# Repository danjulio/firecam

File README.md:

# firecam
 ESP32 code for the Fire CAM Thermal Imager

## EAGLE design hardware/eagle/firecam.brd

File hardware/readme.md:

## FireCAM Hardware
This directory contains hardware design files.  Schematic entry and PCB layout was done using Eagle 7.7.

* display_mount - DXF and SVG files for a laser cut plastic display mount, OpenSCAD and STL files for a 3-piece 3D printed base and display mount.
* documentation - BOM, schematic, PCB image and helpful list of componentst to load on the PCB.
* eagle - Schematic and PCB Layout design files.
* gerber - PCB gerber files
* stencil - Stencil gerber files

### Parts
Two shared Mouser BOMs are available for most of the components.

1. [FireCAM Rev 3 PCB Parts](https://www.mouser.com/ProjectManager/ProjectDetail.aspx?AccessID=e3b4e6fe5d) - Parts for direct mounting on the PCB.
2. [FireCAM Rev 3 Assembly Parts](https://www.mouser.com/ProjectManager/ProjectDetail.aspx?AccessID=ba0938d0f0) - Additional assembly parts.

In addition a commonly available 2.8" ILI9341/XPT2046 LCD display is used.  I have successfully sourced many units from the [HiLetGo](https://www.amazon.com/HiLetgo-240X320-Resolution-Display-ILI9341/dp/B073R7BH1B) store on Amazon but they are available from many sources.  You will also need some flexible 28 AWG silicon hook-up wire and heat shrink to make the Temperature Sensor and LCD wiring harnesses and a Micro-SD Card.

### Main PCB

### Subassemblies

#### Temperature probe
The TMP36 temperature sensor is connected to a 3-pin male 0.1" (2.54mm) using 3 2" (51 mm) 28 AWG wires.  Heatshrink each individual connection and the wire assembly to each of the connector and temperature sensor.  Note the orientation of the sensor relative to the connections on the PCB.

#### Display wiring harness
The Display harness contains the shared SPI bus for the LCD and Touchscreen, control, and power signals.  The shared SPI bus signals are connected at the display side in order to minimize signal reflections.

#### 3D Printed Base and Display Mount
A base and two-piece display mount may be printed by slicing the STL files for your particular printer.  The STL was generated using OpenSCAD and the source files included here.

#### Laser Cut Display Mount
The display mount is designed to be cut from a piece of 1/8" plastic on a laser cutter.

### Enclosure
FireCAM is released without an enclosure as the original client for the project built their own custom enclosure for it.

### Expansion Ports

1. I2C Bus
2. ADC inputs A0 and A1 (not currently used by the firmware)

### Important Notes

1. Do not insert the LiPo battery backwards!  This will damage the camera electronics.
2. The RTC has a higher-than normal draw from the coin cell until it has been initialized.  Load firmware before inserting the coin cell and then immediately power on the camera to initialize the RTC (even if it has the wrong time).
3. Do not enable WiFi unless the antenna is connected.  It is possible to damage the ESP32 without an antenna.
4. The camera is charged from the USB port.  It will take a maximum of 500 mA from this port if it detects a charger attached (D+ connected to D-) or the USB port has been enumerated by an attached computer.  It will take a maximum of 100 mA from this port when attached to a computer but not enumerated.  It will suspect power draw when the USB bus is suspended (e.g. computer is put to sleep).  Current is shared between charging the battery and power the camera so the battery will charge faster if the camera is powered off.  The red LED lights while charging.  It will not charge if D+/D- are not connected together or connected to a computer USB port.  Most USB chargers will work.

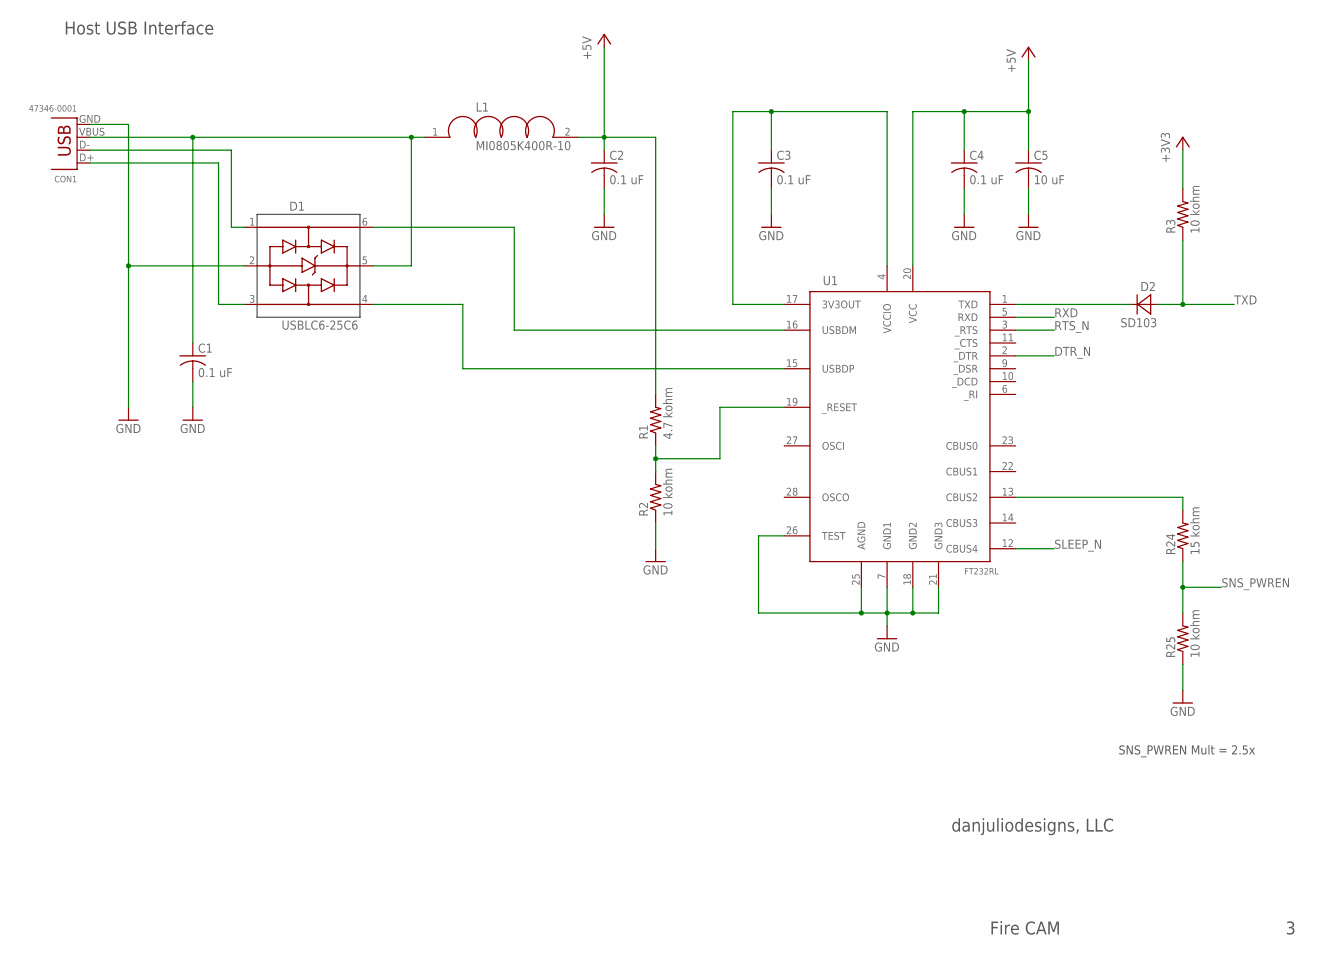
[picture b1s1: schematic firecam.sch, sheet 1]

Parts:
C1, C2, C3, C4: 0.1 uF; C0603
C5: 10 uF; C0603
CON1: 47346-0001; USB_MICROB_SMT
D1: USBLC6-25C6; SOT23-6
D2: SD103; SOD123
L1: MI0805K400R-10; L0805
R1: 4.7 kohm; R0603
R2, R3, R25: 10 kohm; R0603
R24: 15 kohm; R0603
U1: FT232RL; SSOP28DB

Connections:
+3V3: R3.2; also elsewhere on the board
+5V: C2.1, C4.1, C5.1, L1.2, R1.2, U1.20 (VCC); also elsewhere on the board
DTR_N: U1.2 (_DTR); also elsewhere on the board
GND: C1.2, C2.2, C3.2, C4.2, C5.2, CON1.GND, D1.2 (GND), R2.1, R25.1, U1.7 (GND1), U1.18 (GND2), U1.21 (GND3), U1.25 (AGND), U1.26 (TEST); also elsewhere on the board
unnamed: C1.1, CON1.VBUS, D1.5 (VBUS), L1.1
unnamed: CON1.D+, D1.3 (IO2)
unnamed: CON1.D-, D1.1 (IO1)
unnamed: C3.1, U1.4 (VCCIO), U1.17 (3V3OUT)
unnamed: D2.C, U1.1 (TXD)
unnamed: D1.6 (IO1$1), U1.16 (USBDM)
unnamed: D1.4 (IO2$1), U1.15 (USBDP)
unnamed: R1.1, R2.2, U1.19 (_RESET)
unnamed: R24.2, U1.13 (CBUS2)
RTS_N: U1.3 (_RTS); also elsewhere on the board
RXD: U1.5 (RXD); also elsewhere on the board
SLEEP_N: U1.12 (CBUS4); also elsewhere on the board
SNS_PWREN: R24.1, R25.2; also elsewhere on the board
TXD: D2.A, R3.1; also elsewhere on the board

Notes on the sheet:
danjuliodesigns, LLC
Fire CAM
Host USB Interface
SNS_PWREN Mult = 2.5x

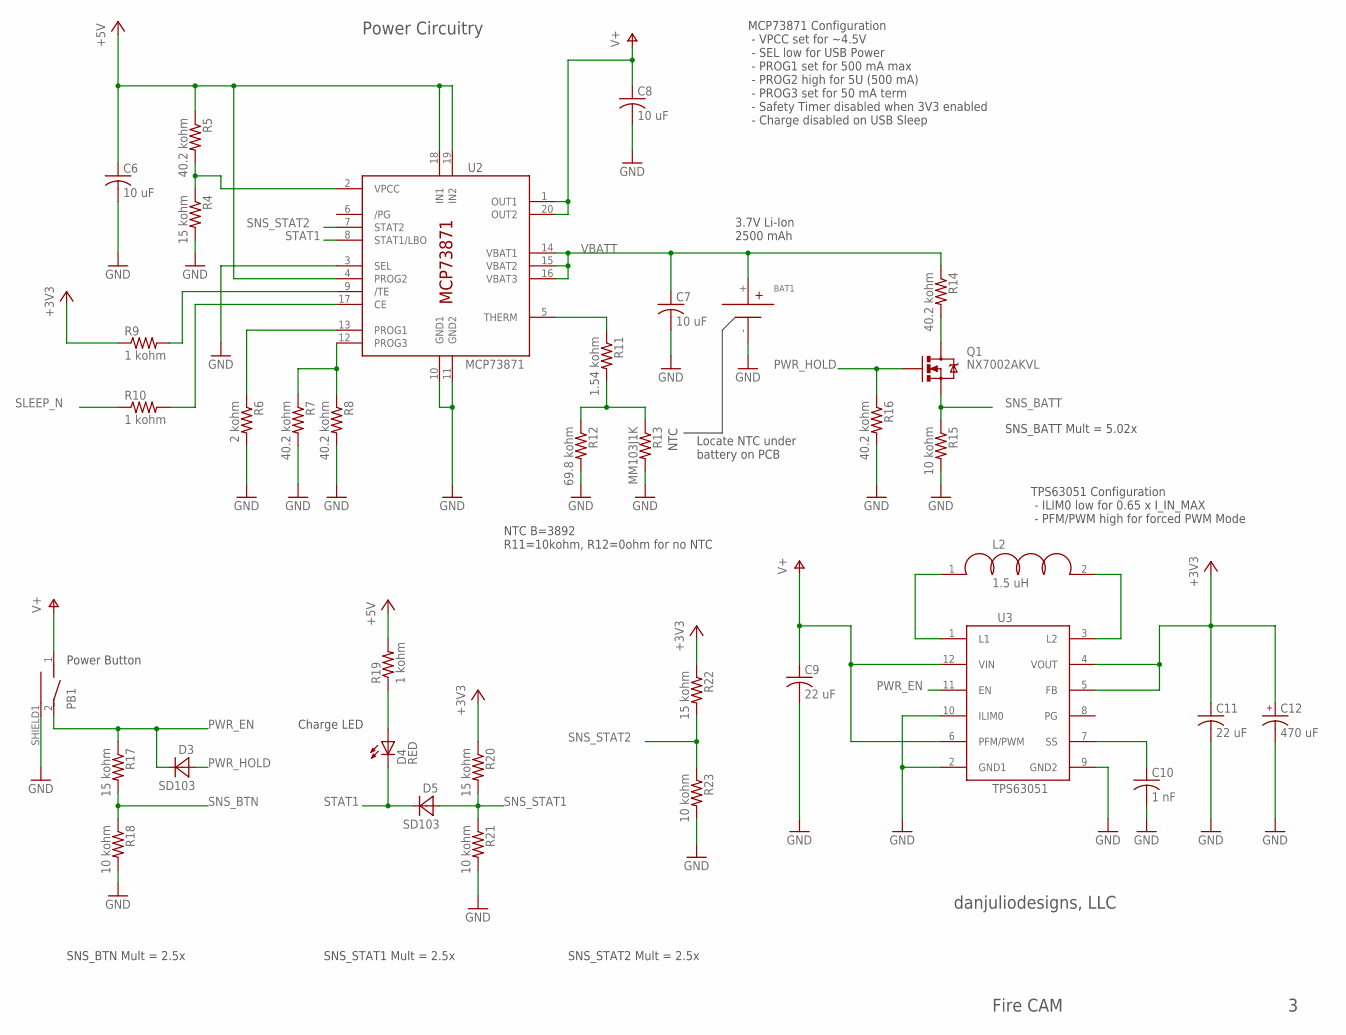
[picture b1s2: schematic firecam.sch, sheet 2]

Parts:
BAT1: 18650_BATTERYTH; KEYSTONE_1043
C6, C7, C8: 10 uF; C0603
C9, C11: 22 uF; C0603
C10: 1 nF; C0603
C12: 470 uF; ECAP-0606
D3, D5: SD103; SOD123
D4: RED; LUMEX_3MM_SMT
L2: 1.5 uH; L1008
PB1: PB_SMT_SIDEPTS645; PTS645_SIDE_TH
Q1: NX7002AKVL; SOT23-3
R4, R17, R20, R22: 15 kohm; R0603
R5, R7, R8, R14, R16: 40.2 kohm; R0603
R6: 2 kohm; R0603
R9, R10, R19: 1 kohm; R0603
R11: 1.54 kohm; R0603
R12: 69.8 kohm; R0603
R13: MM103J1K; R0603
R15, R18, R21, R23: 10 kohm; R0603
U2: MCP73871; QFN20
U3: TPS63051; HOTROD_QFN12

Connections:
+3V3: C11.1, C12.+ (1), R9.1, R20.1, R22.1, U3.4 (VOUT), U3.5 (FB); also elsewhere on the board
+5V: C6.1, R5.1, R19.2, U2.4 (PROG2), U2.18 (IN1), U2.19 (IN2); also elsewhere on the board
GND: BAT1.-, C6.2, C7.2, C8.2, C9.2, C10.2, C11.2, C12.- (2), PB1.SHIELD1 (CASE), R4.2, R6.2, R7.2, R8.2, R12.2, R13.2, R15.2, R16.2, R18.2, R21.2, R23.2, U2.3 (SEL), U2.10 (GND1), U2.11 (GND2), U3.2 (GND1), U3.9 (GND2), U3.10 (ILIM0); also elsewhere on the board
unnamed: R4.1, R5.2, U2.2 (VPCC)
unnamed: R6.1, U2.13 (PROG1)
unnamed: R7.1, R8.1, U2.12 (PROG3)
unnamed: R9.2, U2.9 (/TE)
unnamed: R10.2, U2.17 (CE)
unnamed: R11.1, U2.5 (THERM)
unnamed: L2.1, U3.1 (L1)
unnamed: Q1.3 (D), R14.2
unnamed: D4.P$1 (A), R19.1
unnamed: R11.2, R12.1, R13.1
unnamed: L2.2, U3.3 (L2)
unnamed: C10.1, U3.7 (SS)
PWR_EN: D3.C, PB1.2, R17.1, U3.11 (EN); also elsewhere on the board
PWR_HOLD: D3.A, Q1.1 (G), R16.1; also elsewhere on the board
SLEEP_N: R10.1; also elsewhere on the board
SNS_BATT: Q1.2 (S), R15.1; also elsewhere on the board
SNS_BTN: R17.2, R18.1; also elsewhere on the board
SNS_STAT1: D5.A, R20.2, R21.1; also elsewhere on the board
SNS_STAT2: R22.2, R23.1, U2.7 (STAT2); also elsewhere on the board
STAT1: D4.P$2 (C), D5.C, U2.8 (STAT1/LBO)
V+: C8.1, C9.1, PB1.1, U2.1 (OUT1), U2.20 (OUT2), U3.6 (PFM/PWM), U3.12 (VIN); also elsewhere on the board
VBATT: BAT1.+, C7.1, R14.1, U2.14 (VBAT1), U2.15 (VBAT2), U2.16 (VBAT3)

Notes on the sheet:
danjuliodesigns, LLC
Power Button
Charge LED
Fire CAM
Power Circuitry
3.7V Li-Ion 2500 mAh
MCP73871 Configuration - VPCC set for ~4.5V - SEL low for USB Power - PROG1 set for 500 mA max - PROG2 high for 5U (500 mA) - PROG3 set for 50 mA term - Safety Timer disabled when 3V3 enabled - Charge disabled on USB Sleep
TPS63051 Configuration - ILIM0 low for 0.65 x I_IN_MAX - PFM/PWM high for forced PWM Mode
NTC
Locate NTC under battery on PCB
SNS_BTN Mult = 2.5x
SNS_STAT1 Mult = 2.5x
SNS_STAT2 Mult = 2.5x
SNS_BATT Mult = 5.02x
NTC B=3892 R11=10kohm, R12=0ohm for no NTC

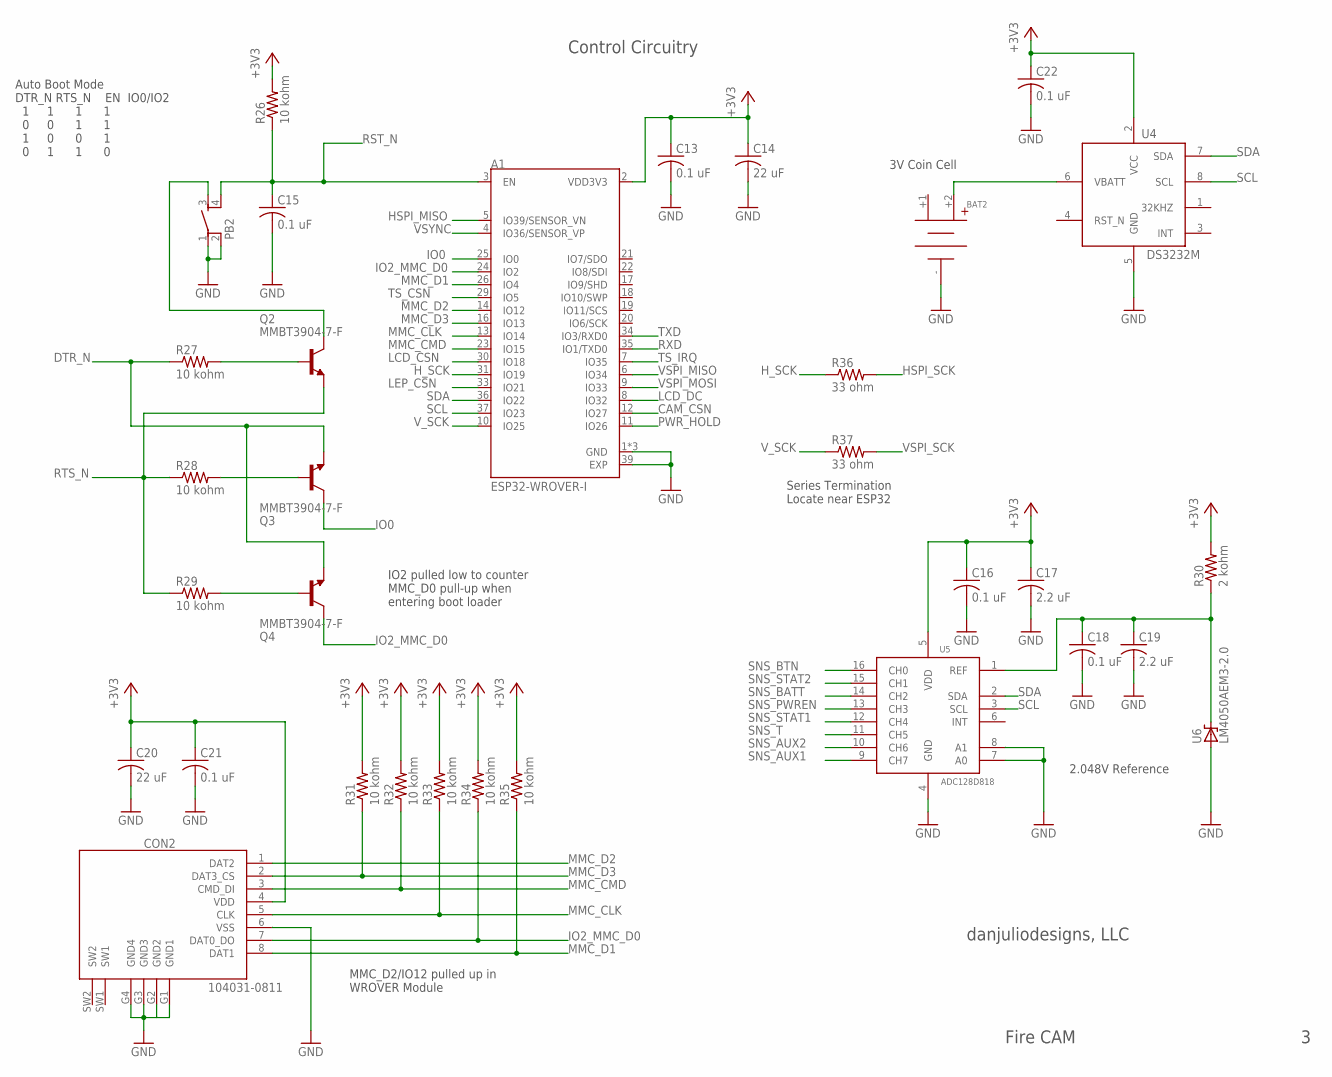
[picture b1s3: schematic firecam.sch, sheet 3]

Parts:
A1: ESP32-WROVER-I; XCVR_ESP32-WROVER-I
BAT2: COIN_CELL12MM; KEYSTONE_3001
C13, C15, C16, C18, C21, C22: 0.1 uF; C0603
C14, C20: 22 uF; C0603
C17, C19: 2.2 uF; C0603
CON2: 104031-0811; MOLEX_1040310811
PB2: PB_TACT_4SMTR92; CK_PTS645_SMT
Q2, Q3, Q4: MMBT3904-7-F; SOT23-BEC
R26, R27, R28, R29, R31, R32, R33, R34, R35: 10 kohm; R0603
R30: 2 kohm; R0603
R36, R37: 33 ohm; R0603
U4: DS3232M; SO8
U5: ADC128D818; SSOP16
U6: LM4050AEM3-2.0; SOT23-3

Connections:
+1: BAT2.+1
+3V3: A1.2 (VDD3V3), C13.1, C14.1, C16.1, C17.1, C20.1, C21.1, C22.1, CON2.4 (VDD), R26.2, R30.2, R31.2, R32.2, R33.2, R34.2, R35.2, U4.2 (VCC), U5.5 (VDD); also elsewhere on the board
CAM_CSN: A1.12 (IO27); also elsewhere on the board
DTR_N: Q3.E, Q4.E, R27.1; also elsewhere on the board
GND: A1.1 (GND), A1.15 (GND), A1.38 (GND), A1.39 (EXP), BAT2.-, C13.2, C14.2, C15.2, C16.2, C17.2, C18.2, C19.2, C20.2, C21.2, C22.2, CON2.6 (VSS), CON2.G1 (GND1), CON2.G2 (GND2), CON2.G3 (GND3), CON2.G4 (GND4), PB2.1, PB2.2, U4.5 (GND), U5.4 (GND), U5.7 (A0), U5.8 (A1), U6.2 (A); also elsewhere on the board
HSPI_MISO: A1.5 (IO39/SENSOR_VN); also elsewhere on the board
HSPI_SCK: R36.2; also elsewhere on the board
H_SCK: A1.31 (IO19), R36.1
IO0: A1.25 (IO0), Q3.C
IO2_MMC_D0: A1.24 (IO2), CON2.7 (DAT0_DO), Q4.C, R34.1
LCD_CSN: A1.30 (IO18); also elsewhere on the board
LCD_DC: A1.8 (IO32); also elsewhere on the board
LEP_CSN: A1.33 (IO21); also elsewhere on the board
MMC_CLK: A1.13 (IO14), CON2.5 (CLK), R33.1
MMC_CMD: A1.23 (IO15), CON2.3 (CMD_DI), R32.1
MMC_D1: A1.26 (IO4), CON2.8 (DAT1), R35.1
MMC_D2: A1.14 (IO12), CON2.1 (DAT2)
MMC_D3: A1.16 (IO13), CON2.2 (DAT3_CS), R31.1
unnamed: C18.1, C19.1, R30.1, U5.1 (REF), U6.1 (C)
unnamed: BAT2.+2, U4.6 (VBATT)
unnamed: PB2.3, Q2.C
unnamed: Q2.B, R27.2
unnamed: Q3.B, R28.2
unnamed: Q4.B, R29.2
PWR_HOLD: A1.11 (IO26); also elsewhere on the board
RST_N: A1.3 (EN), C15.1, PB2.4, R26.1; also elsewhere on the board
RTS_N: Q2.E, R28.1, R29.1; also elsewhere on the board
RXD: A1.35 (IO1/TXD0); also elsewhere on the board
SCL: A1.37 (IO23), U4.8 (SCL), U5.3 (SCL); also elsewhere on the board
SDA: A1.36 (IO22), U4.7 (SDA), U5.2 (SDA); also elsewhere on the board
SNS_AUX1: U5.9 (CH7); also elsewhere on the board
SNS_AUX2: U5.10 (CH6); also elsewhere on the board
SNS_BATT: U5.14 (CH2); also elsewhere on the board
SNS_BTN: U5.16 (CH0); also elsewhere on the board
SNS_PWREN: U5.13 (CH3); also elsewhere on the board
SNS_STAT1: U5.12 (CH4); also elsewhere on the board
SNS_STAT2: U5.15 (CH1); also elsewhere on the board
SNS_T: U5.11 (CH5); also elsewhere on the board
TS_CSN: A1.29 (IO5); also elsewhere on the board
TS_IRQ: A1.7 (IO35); also elsewhere on the board
TXD: A1.34 (IO3/RXD0); also elsewhere on the board
VSPI_MISO: A1.6 (IO34); also elsewhere on the board
VSPI_MOSI: A1.9 (IO33); also elsewhere on the board
VSPI_SCK: R37.2; also elsewhere on the board
VSYNC: A1.4 (IO36/SENSOR_VP); also elsewhere on the board
V_SCK: A1.10 (IO25), R37.1

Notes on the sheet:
IO2 pulled low to counter MMC_D0 pull-up when entering boot loader
Auto Boot Mode DTR_N RTS_N EN IO0/IO2 1 1 1 1 0 0 1 1 1 0 0 1 0 1 1 0
MMC_D2/IO12 pulled up in WROVER Module
Control Circuitry
3V Coin Cell
Series Termination Locate near ESP32
2.048V Reference
danjuliodesigns, LLC
Fire CAM

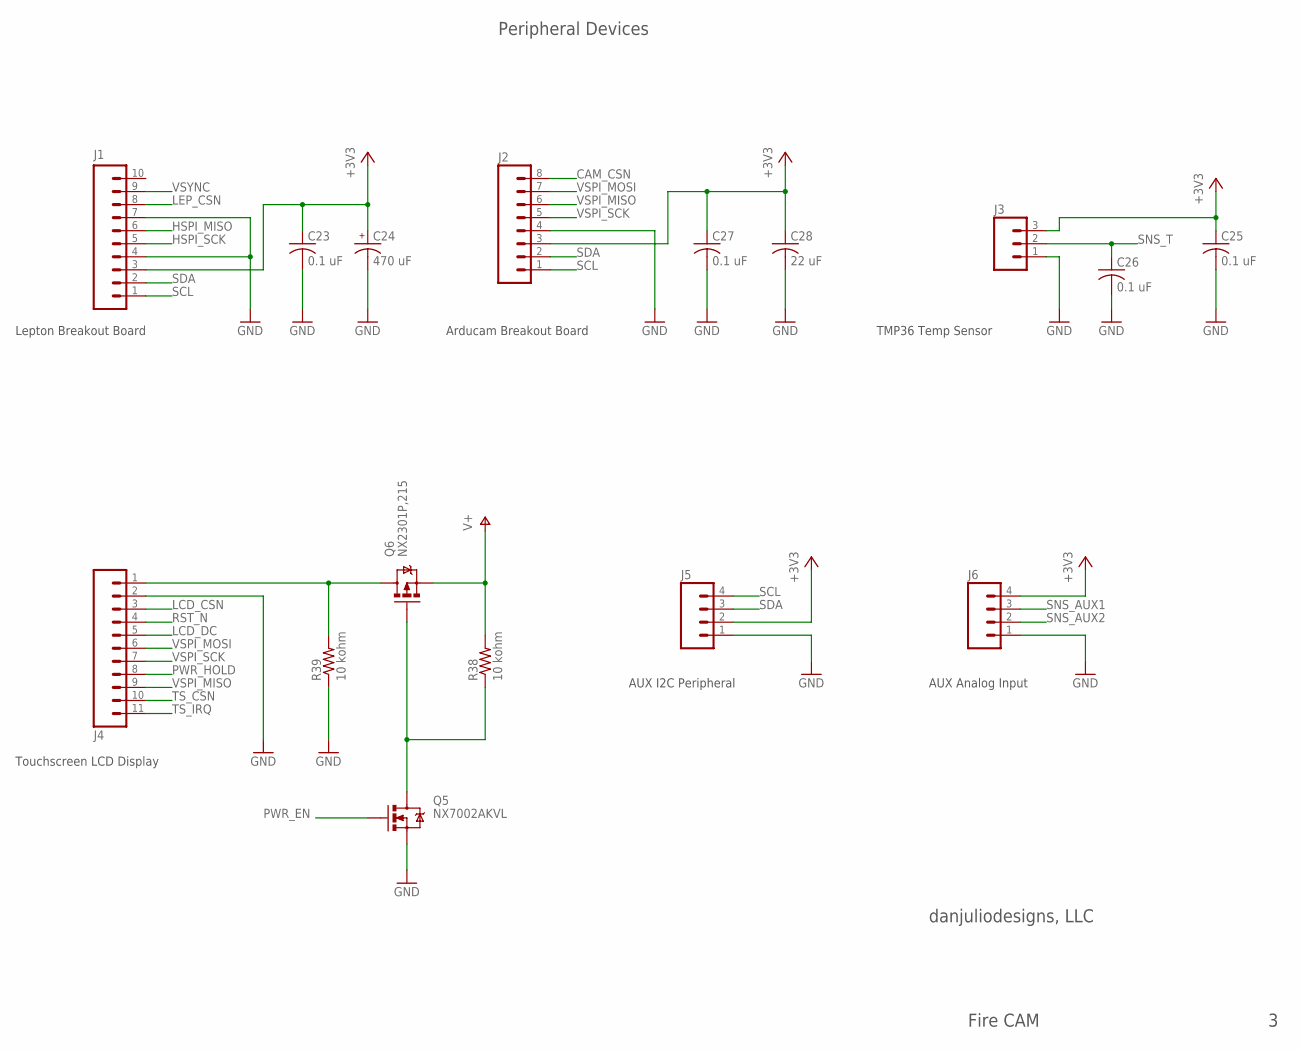
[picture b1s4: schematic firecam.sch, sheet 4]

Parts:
C23, C25, C26, C27: 0.1 uF; C0603
C24: 470 uF; ECAP-0606
C28: 22 uF; C0603
J1: M10SILK_FEMALE_PTH; 1X10
J2: M08SILK_FEMALE_PTH; 1X08
J3: M03PTH; 1X03
J4: M11PTH; 1X11
J5, J6: M04PTH; 1X04
Q5: NX7002AKVL; SOT23-3
Q6: NX2301P,215; SOT23-3
R38, R39: 10 kohm; R0603

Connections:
+3V3: C23.1, C24.+ (1), C25.1, C27.1, C28.1, J1.3, J2.3, J3.3, J5.2, J6.4; also elsewhere on the board
CAM_CSN: J2.8; also elsewhere on the board
GND: C23.2, C24.- (2), C25.2, C26.2, C27.2, C28.2, J1.4, J1.7, J2.4, J3.1, J4.2, J5.1, J6.1, Q5.2 (S), R39.1; also elsewhere on the board
HSPI_MISO: J1.6; also elsewhere on the board
HSPI_SCK: J1.5; also elsewhere on the board
LCD_CSN: J4.3; also elsewhere on the board
LCD_DC: J4.5; also elsewhere on the board
LEP_CSN: J1.8; also elsewhere on the board
unnamed: J4.1, Q6.3 (D), R39.2
unnamed: Q5.3 (D), Q6.1 (G), R38.1
PWR_EN: Q5.1 (G); also elsewhere on the board
PWR_HOLD: J4.8; also elsewhere on the board
RST_N: J4.4; also elsewhere on the board
SCL: J1.1, J2.1, J5.4; also elsewhere on the board
SDA: J1.2, J2.2, J5.3; also elsewhere on the board
SNS_AUX1: J6.3; also elsewhere on the board
SNS_AUX2: J6.2; also elsewhere on the board
SNS_T: C26.1, J3.2; also elsewhere on the board
TS_CSN: J4.10; also elsewhere on the board
TS_IRQ: J4.11; also elsewhere on the board
V+: Q6.2 (S), R38.2; also elsewhere on the board
VSPI_MISO: J2.6, J4.9; also elsewhere on the board
VSPI_MOSI: J2.7, J4.6; also elsewhere on the board
VSPI_SCK: J2.5, J4.7; also elsewhere on the board
VSYNC: J1.9; also elsewhere on the board

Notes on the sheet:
Lepton Breakout Board
Arducam Breakout Board
TMP36 Temp Sensor
AUX I2C Peripheral
Touchscreen LCD Display
AUX Analog Input
Peripheral Devices
danjuliodesigns, LLC
Fire CAM

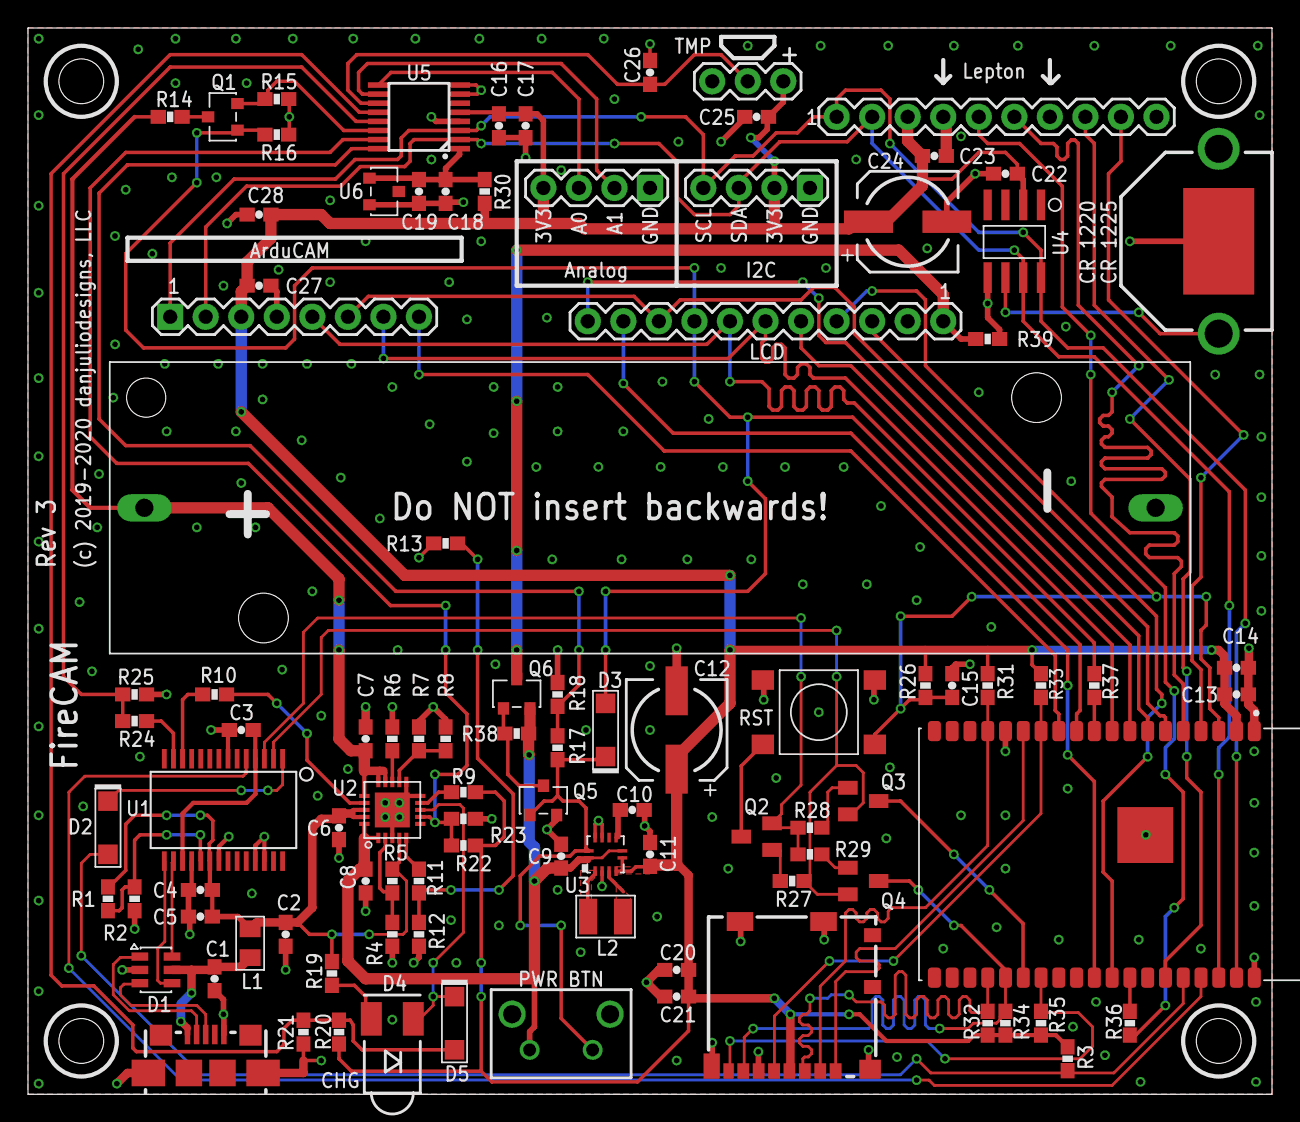
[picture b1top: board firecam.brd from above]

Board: 2 copper layers, 88.9 x 76.2 mm, 99 parts (0 on the bottom side), 74 nets.

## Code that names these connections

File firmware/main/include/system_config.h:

/*
 * System Configuration File
 *
 * Contains system definition and configurable items.
 *
 * Copyright 2020 Dan Julio
 *
 * This file is part of firecam.
 *
 * firecam is free software: you can redistribute it and/or modify
 * it under the terms of the GNU General Public License as published by
 * the Free Software Foundation, either version 3 of the License, or
 * (at your option) any later version.
 *
 * firecam is distributed in the hope that it will be useful,
 * but WITHOUT ANY WARRANTY; without even the implied warranty of
 * MERCHANTABILITY or FITNESS FOR A PARTICULAR PURPOSE.  See the
 * GNU General Public License for more details.
 *
 * You should have received a copy of the GNU General Public License
 * along with firecam.  If not, see <https://www.gnu.org/licenses/>.
 *
 */
#ifndef SYSTEM_CONFIG_H
#define SYSTEM_CONFIG_H

#include "esp_system.h"
#include "cci.h"
#include "ov2640.h"


// ======================================================================================
// System debug
//

// Undefine to include the system monitoring task (included only for debugging/tuning)
//#define INCLUDE_SYS_MON



// ======================================================================================
// System hardware definitions
//

//
// IO Pins
//   Lepton uses HSPI (no MOSI)
//   ArduCam, LCD and TS use VSPI
//
#define TS_CSN_IO         5
#define LCD_CSN_IO        18
#define HSPI_SCK_IO       19
#define LEP_CSN_IO        21
#define I2C_MASTER_SDA_IO 22
#define I2C_MASTER_SCL_IO 23
#define VSPI_SCK_IO       25
#define PWR_HOLD_IO       26
#define CAM_CSN_IO        27
#define LCD_DC_IO         32
#define VSPI_MOSI_IO      33
#define VSPI_MISO_IO      34
#define TS_IRQ_IO         35
#define LEP_VSYNC_IO      36
#define HSPI_MISO_IO      39


//
// Hardware Configuration
//

// I2C
#define I2C_MASTER_NUM     1
#define I2C_MASTER_FREQ_HZ 100000

// SPI
#define LEP_SPI_HOST    HSPI_HOST
#define CAM_SPI_HOST    VSPI_HOST
#define LCD_SPI_HOST    VSPI_HOST
#define TS_SPI_HOST     VSPI_HOST
#define HSPI_DMA_NUM    1
#define VSPI_DMA_NUM    2
#define LEP_SPI_FREQ_HZ 16000000
#define LCD_SPI_FREQ_HZ 16000000
#define CAM_SPI_FREQ_HZ  4000000
#define TS_SPI_FREQ_HZ   2000000


// ======================================================================================
// System configuration
//

// Little VGL buffer update size
#define LVGL_DISP_BUF_SIZE (320 * 40)

// Little VGL Touchpanel configuration (a bit of a hack - it should be calibrated)
#define LVGL_TOUCH_X_MIN    360
#define LVGL_TOUCH_Y_MIN    270
#define LVGL_TOUCH_X_MAX    3900
#define LVGL_TOUCH_Y_MAX    3800
#define LVGL_TOUCH_INVERT_X 1
#define LVGL_TOUCH_INVERT_Y 1

// Little VGL evaluation rate (mSec)
#define LVGL_EVAL_MSEC      10


// ArduCAM image resolution
//  Undefine for 640x480 resolution, otherwise 320x240
//  Note: CAM_RES_HIGH also sets the jpeg decoder scale factor in render_jpg.c
#define CAM_RES_HIGH

#ifdef CAM_RES_HIGH
#define CAM_SIZE_SPEC       OV2640_640x480
#define CAM_JPEG_WIDTH      640
#else
#define CAM_SIZE_SPEC       OV2640_320x240
#define CAM_JPEG_WIDTH      320
#endif


// ArduCAM max jpg image size (based on CAM_SIZE_SPEC)
#ifdef CAM_RES_HIGH
#define CAM_MAX_JPG_LEN     65536
#else
#define CAM_MAX_JPG_LEN     32768
#endif

// Lepton default gain mode
#define LEP_DEF_GAIN_MODE  LEP_SYS_GAIN_MODE_HIGH

// Combined image (ArduCAM + Lepton + Metadata) json object text size
// Based on the following items:
//   1. Base64 encoded ArduCAM maximum image size: CAM_MAX_JPG_LEN*4 / 3
//   2. Base64 encoded Lepton image size: (160x120x2)*4 / 3
//   3. Metadata text size: 2048
//   4. Json object overhead (child names, formatting characters, NLs): 256
// Manually calculate this and round to 4-byte boundary
#ifdef CAM_RES_HIGH
#define JSON_MAX_IMAGE_TEXT_LEN (1024 * 160)
#else
#define JSON_MAX_IMAGE_TEXT_LEN (1024 * 128)
#endif

// Max command response json object text size
#define JSON_MAX_RSP_TEXT_LEN   1024

// Maximum incoming command json string length (large enough for longest command)
#define JSON_MAX_CMD_TEXT_LEN   256

// Maximum TCP/IP Socket receiver buffer
//  This should be large enough for the maximum number of command received at a time
//  (probably 2 is ok)
#define CMD_MAX_TCP_RX_BUFFER_LEN 1024

// TCP/IP listening port
#define CMD_PORT 5001


// Recording Intervals and names
#define REC_INT_0_VAL  1
#define REC_INT_0_NAME "1 Second"
#define REC_INT_1_VAL  5
#define REC_INT_1_NAME "5 Seconds"
#define REC_INT_2_VAL  30
#define REC_INT_2_NAME "30 Seconds"
#define REC_INT_3_VAL  60
#define REC_INT_3_NAME "1 Minute"
#define REC_INT_4_VAL  300
#define REC_INT_4_NAME "5 Minutes"
#define REC_INT_5_VAL  1800
#define REC_INT_5_NAME "30 Minutes"
#define REC_INT_6_VAL  3600
#define REC_INT_6_NAME "1 Hour"
#define REC_INT_NUM    7





#endif // SYSTEM_CONFIG_H

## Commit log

2020-02-28 Initial checkin
2020-05-22 Version 2.0 and readme files
    1. Version 2.0 firmware
    a. Support Client WiFi mode - DHCP or Static IP address
    b. Additional camera configuration - Timelapse interval, lepton gain, palettes
    c. New setting screens and other gui changes including additional palettes
    d. New commands to support configuring settings and wifi
    e. Include Lepton telemetry in image files
2020-07-08 Fixed misc items in readmes
2020-07-20 Increased length by 0.25"
2022-07-10 Firmware Revision 2.1
2022-07-14 Added 3D printed base/display mount

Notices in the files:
hardware/eagle/firecam.brd:
(c) 2019-2020 danjuliodesigns, LLC
parts and their libraries:
SparkFun-Connectors: Licensing: Creative Commons ShareAlike 4.0 International - https://creativecommons.org/licenses/by-sa/4.0
